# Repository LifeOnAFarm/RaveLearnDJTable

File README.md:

# Fisher-Price: Rave & Repeat DJ Table

A Raspberry Pi rebuild of a Fisher-Price kids' DJ table toy: an eight-key musical play
table running on a **Raspberry Pi Zero 2 W**, written in Python 3.11+.

Full run down of the hardware setup can be found [here](https://nastypieceof.work/raveandrepeat).
The PCB files, parts list and wiring notes are in [hardware/](hardware/README.md).

## Software guides

1. [Installation](docs/INSTALL.md): from a blank SD card to a finished table.
2. [Replacing sounds](docs/SAMPLES.md): songs, words, beats, drums, the recording prompt
   and announcements.

## What it does

The table has three keyboard modes, chosen on its web page or by holding the mode button
for 5 seconds.

**Learning.** The keys say their colour and shape in English (Level 1) or Irish (Level 2),
or play notes (Level 3). The **NumPad** (the single button made to look like a number pad)
plays a random song. Record asks for a message, records
3 seconds of your voice and plays it back as a pitched-up remix over a beat. There are four
music themes, each with its own instruments, songs and beats: **Teenage Disco, House, Punk
and Baby Raver**. A tap on the mode button changes theme.

**Music Maker.** Build a loop in three layers: melody (Level 1), drums (Level 2) and your
own voice as an instrument (Level 3).

**Bluetooth.** Phone music plays through the table and the keys play along.

| Control | Learning | Music Maker | Bluetooth |
| --- | --- | --- | --- |
| Keys | Colour/shape words or notes | Notes, drums or your voice | Notes over the music |
| Level | 1 English, 2 Irish, 3 notes | 1 melody, 2 drums, 3 voice | 1 Punk, 2 Teenage Disco, 3 House sounds |
| Tone | Three sounds per theme | Three instruments, kits or voice characters | Three instruments |
| Volume | Low / medium / high | Low / medium / high | Low / medium / high |
| Record | Voice remix | Hold: record a layer after the count-in. Tap at Level 3: sample a sound to play on the keys | Off |
| NumPad | Random song, or stop | Tap: play/pause. Hold 2 s: clear this layer. Hold 5 s: clear all | Tap: play/pause. Hold: next track |
| Platter | Bends notes and song speed; spun on its own, plays a scratch | Bends notes and loop speed | |

Spoken announcements say when the theme, mode or Level changes.

**Turning it off:** hold the mode button, then Record as well, and keep both held for
10 seconds. The table says it's shutting down and powers off safely. Wait for the Pi's
light to stop flashing before you switch off the power.

In Bluetooth mode the table is visible as **DJTable** for two minutes. Pair with no PIN.
If no phone connects in time, it goes back to Learning.

## Web pages

Open `http://<your-table>:8080` from a phone or computer on the same network.

- **Home:** keyboard mode, music theme and song uploads.
- **Admin:** live test of every button, slider, the platter and the microphone, plus each
  theme's song list.
- **Wi-Fi:** join a new network. If the table can't find a known network, it offers its
  own **DJTable-Setup** network (see the install guide).

## Sounds

Every sound the table needs is in `sounds/`, except the random songs, which you upload
yourself. There are **no commercial songs, licensed samples or personal recordings**.

- The keyboard instruments for every theme (House has chords, stabs and a deep bass in
  F minor) and the remix beats: original, synthesised in code.
- The English and Irish colour and shape words, the spoken announcements and the
  recording prompt.
- The platter scratches.

The Music Maker drum kits are built by the app itself when it starts.

Make the table your own with [Replacing sounds](docs/SAMPLES.md).

## Folder layout

```text
djtable/        the app: audio engine, buttons, platter, web pages
deploy/         install scripts, services, sound overlay
tools/          song volume matcher
sounds/         all of the table's sounds
docs/           install and sound guides
hardware/       PCB Gerbers, schematic, KiCad project, parts list and 3D prints
config.example.json   the table's settings (copied to config.json on install)
```

On the Pi, `config.json`, `assets/` (sounds) and `data/` (songs, recordings, loops) are
created by the installer and are never part of the repository.

## Licence

> Unofficial hobby project. Not affiliated with, endorsed by or sponsored by Fisher-Price
> or Mattel. Fisher-Price is a trademark of its owner, used here only to describe the toy
> this project rebuilds.

MIT source; see [LICENSE](LICENSE). Your own songs and sounds keep their own licences.

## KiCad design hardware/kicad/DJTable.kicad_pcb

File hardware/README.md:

# Hardware

The carrier PCB that turns the toy into a Rave & Repeat table. The full build, with
photos, is on the [project website](https://nastypieceof.work/raveandrepeat).

| File | What it is |
| --- | --- |
| `DJTable-gerbers.zip` | Ready to upload to a PCB maker (JLCPCB, PCBWay and others): copper, mask, silkscreen, outline and drill files. 2 layers. |
| `DJTable-schematic.pdf` | The schematic, for reading without KiCad. |
| `kicad/` | The KiCad 10 project (schematic, PCB and its own footprint library), if you want to change the board. Open `DJTable.kicad_pro`. |

## Read before you build

This is the board revision that was built and works, with these fixes made by hand.
**The PCB files don't include them yet.**

1. **Wire the amp's SD pin to Raspberry Pi header pin 7** (GPIO4). That's pin 7 of the
   Pi's 40-pin header, not of the amp module. The software uses it to mute the amp while
   it loads a new theme. Without it, theme changes crackle.
2. **Wire the amp's GAIN pin to ground.** This sets the amp to 12 dB, louder than the
   9 dB it gives with GAIN left unconnected.
3. **The Raspberry Pi mounts upside-down**, with its chips facing the carrier board. Oops
4. **The toy's original switches don't fit this board**, although that was the plan.
   Use these instead. Both fit the board and work with the toy:
   - **SS-23D03-G4** three-position slide switches for Level and Volume (SW4, SW5).
     They stand about 2 mm taller than the toy's switches, so print the new
     `Switch Cover.STL` (below), or cut about 2 mm off the toy's own switch covers;
   - **PS-12F03-G5** push switches for the three Tone buttons (SW1–SW3). The G4 also
     works, but its shorter plunger needs the board lined up exactly before screwing it in.
5. **Bridge R2** with a 0 Ω resistor or a wire. It connects the Mode button; it was left
   as an option on this board and isn't needed as a resistor.

**For a future board revision:** pick a different three-position slide switch for Level and
Volume, with a body about 5.5 mm tall instead of the SS-23D03-G4's 7.5 mm, so the toy's
original switch covers fit unchanged. No replacement part has been chosen yet.

## Parts

| Qty | Ref | Part | Notes |
| ---: | --- | --- | --- |
| 1 | U1 | Raspberry Pi Zero 2 W | With a 2×20 male header |
| 1 | U1 | 2×20 female socket, 2.54 mm | |
| 1 | U2 | INMP441 microphone module | |
| 1 | U3 | MAX98357A amplifier module (Adafruit-style) | Plus the SD and GAIN wires above |
| 3 | SW1–SW3 | PS-12F03-G5 push switch | Tone |
| 2 | SW4–SW5 | SS-23D03-G4 slide switch, 3-position | Level and Volume; needs the printed switch covers |
| 2 | SW6–SW7 | 6×6 mm tactile switch, through-hole | Record and Mode |
| 1 | R1 | 330 Ω, 1206 | NumPad LED |
| 1 | R2 | 0 Ω, 1206, or a wire | **Bridge it**: connects the Mode button |
| 2 | R6–R7 | 33 Ω, 1206 | I2S clock lines |
| 3 | C2, C3, C4 | 100 nF ceramic, 1206, 16 V+ | |
| 1 | C1 | 220 µF 10 V electrolytic | |
| 1 | C5 | 47 µF 10 V electrolytic | |
| 1 | F1 | Resettable fuse, 2 A hold, 6 V+, 1812 | |
| — | J1–J6 | 2.54 mm pin headers, or solder the wires in | See connectors below |

Off the board:
- an AS5600 magnetic angle module with a diametric magnet, for the platter;
- USB C connector.
- 3D printed parts (below).

Power the table only through J3, never through the Pi's USB port at the same time.

## 3D printed parts

STL files in [`3d-prints/`](3d-prints/).

| Part | What it does | Needed? |
| --- | --- | --- |
| `Platter Mount.STL` | Replaces the toy's platter mount, with a pocket to glue in the AS5600's magnet | Yes |
| `AS5600 Mount.STL` | Holds the AS5600 under the platter; takes a 5 mm LED too if you want one. Replaces the toy's button and LED board | Yes |
| `Mode Button.STL` | A working Mode button. On Learn & Play tables without language changing, that button is only a dummy | Only for those tables |
| `Switch Cover.STL` | Covers for the Level and Volume switches, made for the taller SS-23D03-G4 | Yes, unless you cut about 2 mm off the toy's own covers |
| `Speaker Holder.STL` | Lets you fit a more powerful speaker in place of the original | Optional |

## Connectors

| Connector | Pins |
| --- | --- |
| J1 Keyboard | 1 GND, 2 pink, 3 red, 4 orange, 5 green, 6 yellow, 7 blue, 8 purple, 9 black |
| J2 NumPad button | 1 switch GND, 2 switch, 3 LED −, 4 LED + |
| J3 Power in | 1 +5 V, 2 GND |
| J4, J5 | Spare 5 V outputs (1 +5 V, 2 GND) |
| J6 AS5600 | 1 VCC (3.3 V), 2 OUT (unused), 3 GND, 4 DIR (GND), 5 SCL, 6 SDA, 7 GPO (unused) |

## Raspberry Pi pins

All buttons and switches connect a pin to ground; the software turns on the pull-ups.

| Control | GPIO (BCM) | Header pin |
| --- | --- | --- |
| Keys pink, red, orange, green | 5, 6, 12, 13 | 29, 31, 32, 33 |
| Keys yellow, blue, purple, black | 16, 17, 22, 27 | 36, 11, 15, 13 |
| Tone 1 / 2 / 3 | 7 / 24 / 23 | 26 / 18 / 16 |
| Level 1 / 2 / 3 | 8 / 26 / 25 | 24 / 37 / 22 |
| Volume low / medium / high | 15 / 14 / 9 | 10 / 8 / 21 |
| NumPad | 10 | 19 |
| Record | 11 | 23 |
| Mode | 0 | 27 |
| Amp mute (amp SD) | 4 | 7 |
| I2S bit clock / frame clock | 18 / 19 | 12 / 35 |
| Mic data / speaker data | 20 / 21 | 38 / 40 |
| AS5600 SDA / SCL | 2 / 3 | 3 / 5 |

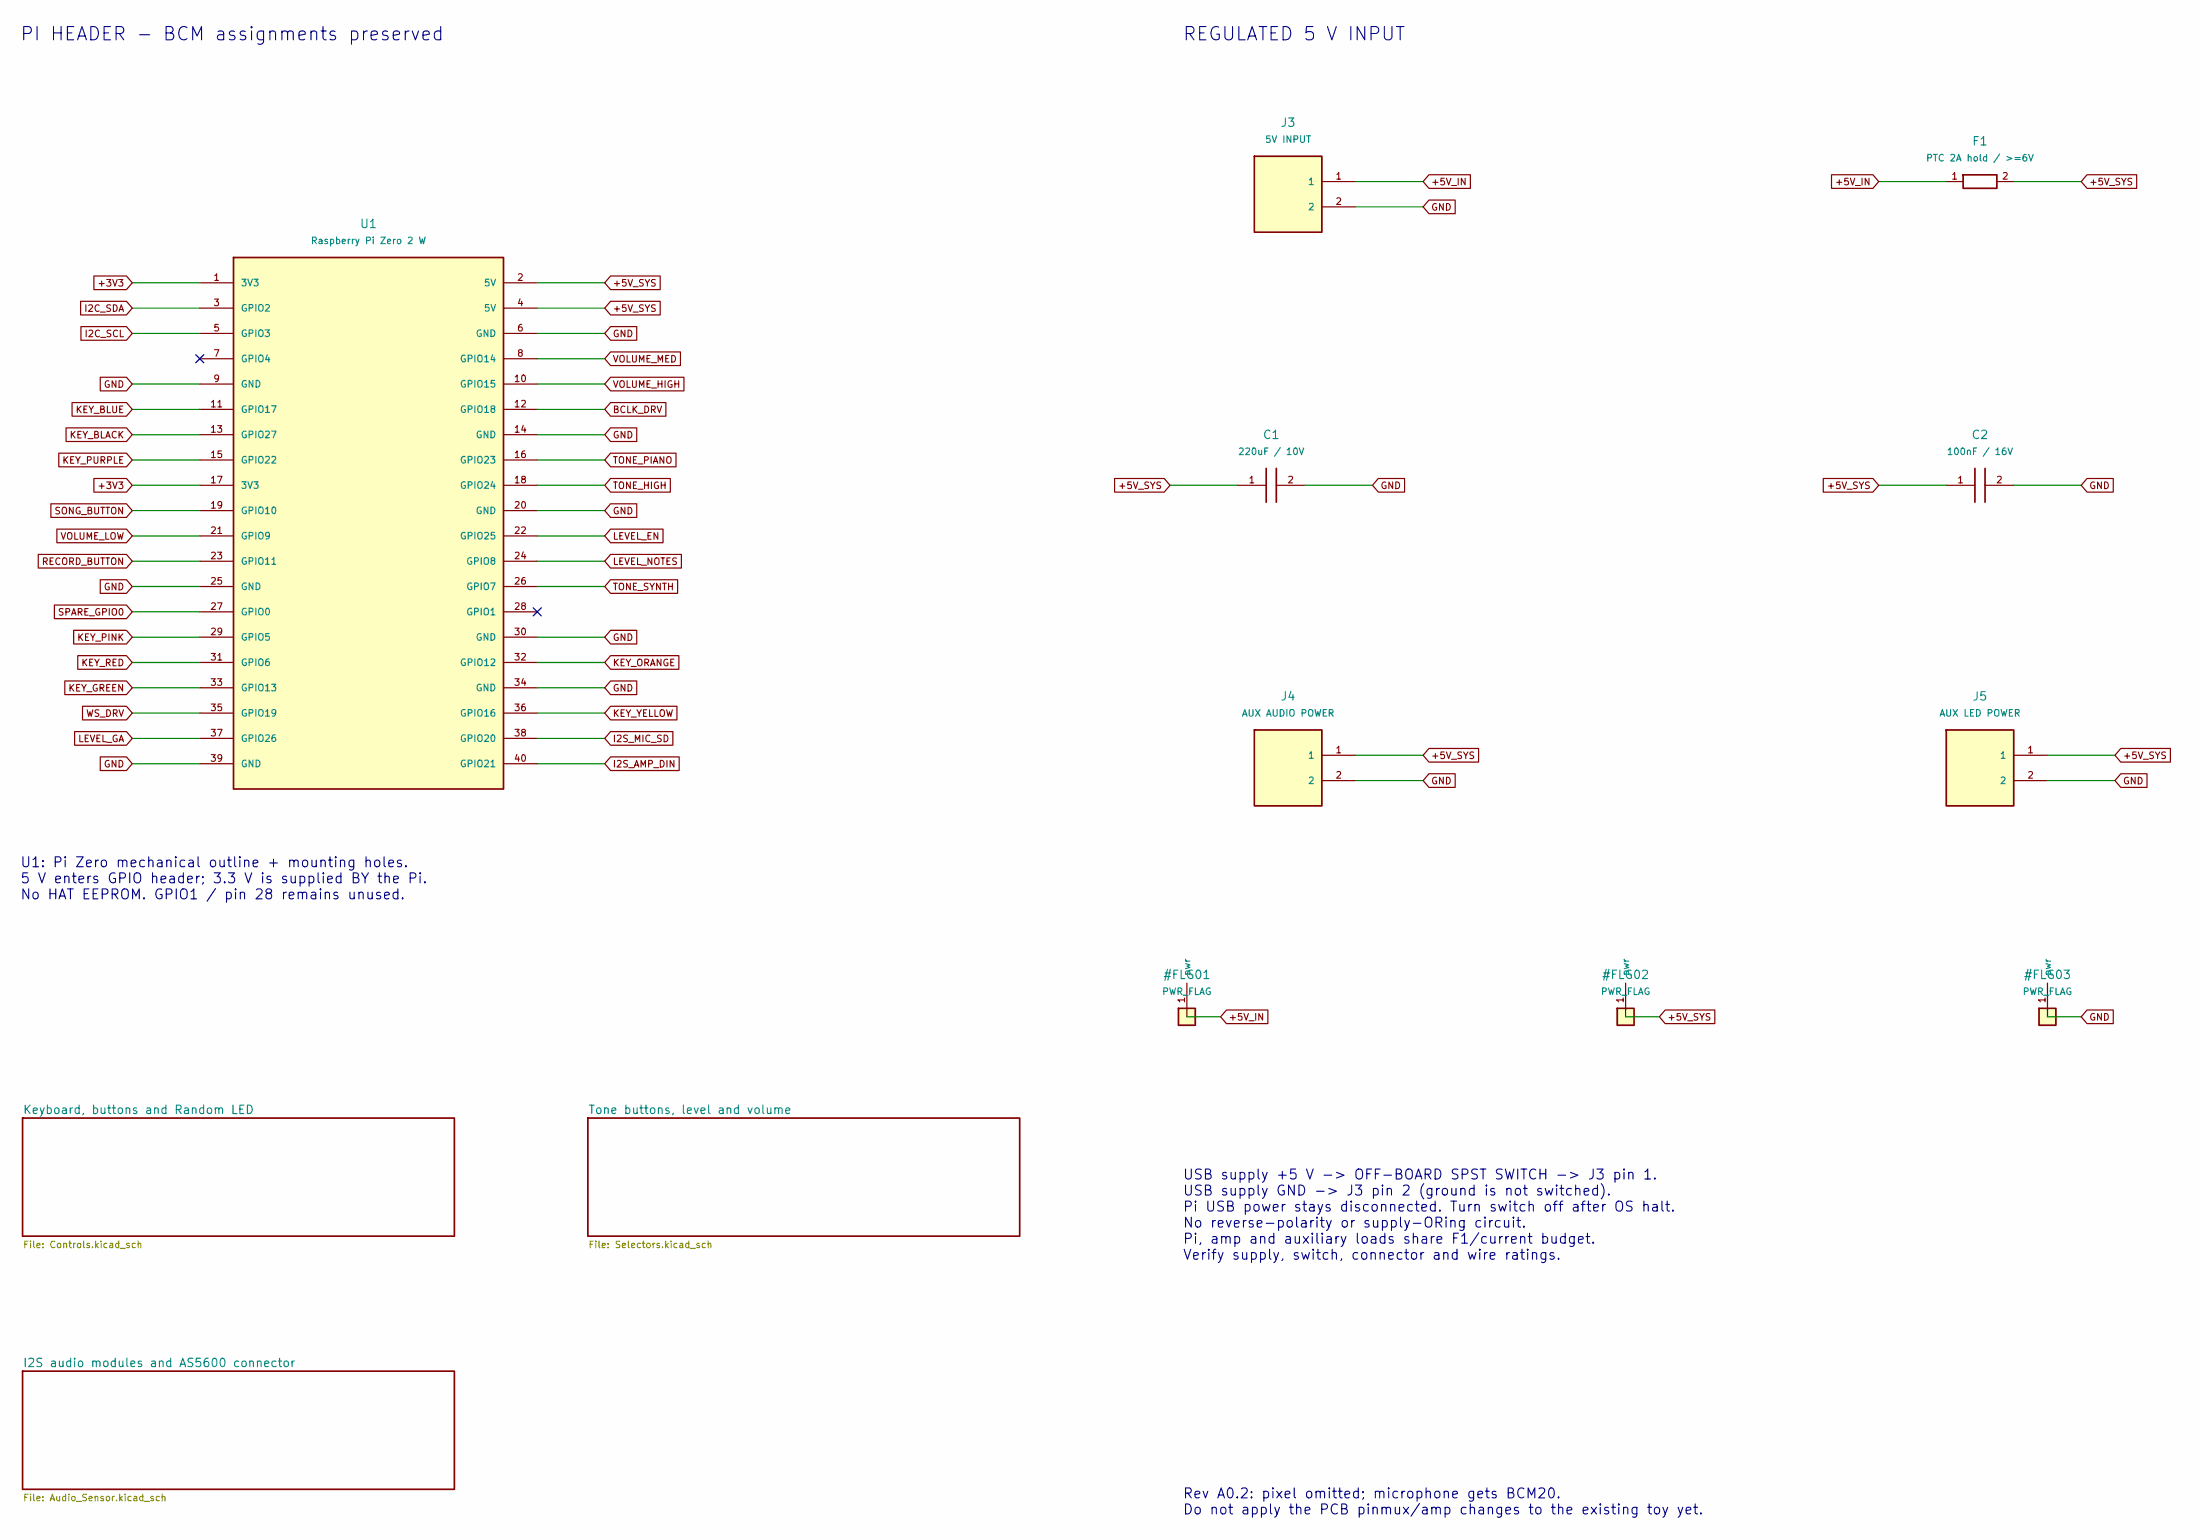
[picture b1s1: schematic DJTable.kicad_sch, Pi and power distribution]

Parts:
C1: 220uF / 10V; CP_Radial_D8.0mm_P3.50mm
C2: 100nF / 16V; C_1206_3216Metric_Pad1.33x1.80mm_HandSolder
F1: PTC 2A hold / >=6V; Fuse_1812_4532Metric
J3: 5V INPUT; PinHeader_1x02_P2.54mm_Vertical
J4: AUX AUDIO POWER; PinHeader_1x02_P2.54mm_Vertical
J5: AUX LED POWER; PinHeader_1x02_P2.54mm_Vertical
U1: Raspberry Pi Zero 2 W; Raspberry_Pi_Zero_Socketed_THT_FaceDown_MountingHoles

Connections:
+3V3: U1.1 (3V3), U1.17 (3V3); also elsewhere on the board
+5V_IN: F1.1, J3.1
+5V_SYS: C1.1, C2.1, F1.2, J4.1, J5.1, U1.2 (5V), U1.4 (5V); also elsewhere on the board
BCLK_DRV: U1.12 (GPIO18); also elsewhere on the board
GND: C1.2, C2.2, J3.2, J4.2, J5.2, U1.6 (GND), U1.9 (GND), U1.14 (GND), U1.20 (GND), U1.25 (GND), U1.30 (GND), U1.34 (GND), U1.39 (GND); also elsewhere on the board
I2C_SCL: U1.5 (GPIO3); also elsewhere on the board
I2C_SDA: U1.3 (GPIO2); also elsewhere on the board
I2S_AMP_DIN: U1.40 (GPIO21); also elsewhere on the board
I2S_MIC_SD: U1.38 (GPIO20); also elsewhere on the board
KEY_BLACK: U1.13 (GPIO27); also elsewhere on the board
KEY_BLUE: U1.11 (GPIO17); also elsewhere on the board
KEY_GREEN: U1.33 (GPIO13); also elsewhere on the board
KEY_ORANGE: U1.32 (GPIO12); also elsewhere on the board
KEY_PINK: U1.29 (GPIO5); also elsewhere on the board
KEY_PURPLE: U1.15 (GPIO22); also elsewhere on the board
KEY_RED: U1.31 (GPIO6); also elsewhere on the board
KEY_YELLOW: U1.36 (GPIO16); also elsewhere on the board
LEVEL_EN: U1.22 (GPIO25); also elsewhere on the board
LEVEL_GA: U1.37 (GPIO26); also elsewhere on the board
LEVEL_NOTES: U1.24 (GPIO8); also elsewhere on the board
RECORD_BUTTON: U1.23 (GPIO11); also elsewhere on the board
SONG_BUTTON: U1.19 (GPIO10); also elsewhere on the board
SPARE_GPIO0: U1.27 (GPIO0); also elsewhere on the board
TONE_HIGH: U1.18 (GPIO24); also elsewhere on the board
TONE_PIANO: U1.16 (GPIO23); also elsewhere on the board
TONE_SYNTH: U1.26 (GPIO7); also elsewhere on the board
VOLUME_HIGH: U1.10 (GPIO15); also elsewhere on the board
VOLUME_LOW: U1.21 (GPIO9); also elsewhere on the board
VOLUME_MED: U1.8 (GPIO14); also elsewhere on the board
WS_DRV: U1.35 (GPIO19); also elsewhere on the board

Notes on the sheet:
PI HEADER - BCM assignments preserved
REGULATED 5 V INPUT
Rev A0.2: pixel omitted; microphone gets BCM20. Do not apply the PCB pinmux/amp changes to the existing toy yet.
USB supply +5 V -> OFF-BOARD SPST SWITCH -> J3 pin 1. USB supply GND -> J3 pin 2 (ground is not switched). Pi USB power stays disconnected. Turn switch off after OS halt. No reverse-polarity or supply-ORing circuit. Pi, amp and auxiliary loads share F1/current budget. Verify supply, switch, connect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
U1: Pi Zero mechanical outline + mounting holes. 5 V enters GPIO header; 3.3 V is supplied BY the Pi. No HAT EEPROM. GPIO1 / pin 28 remains unused.

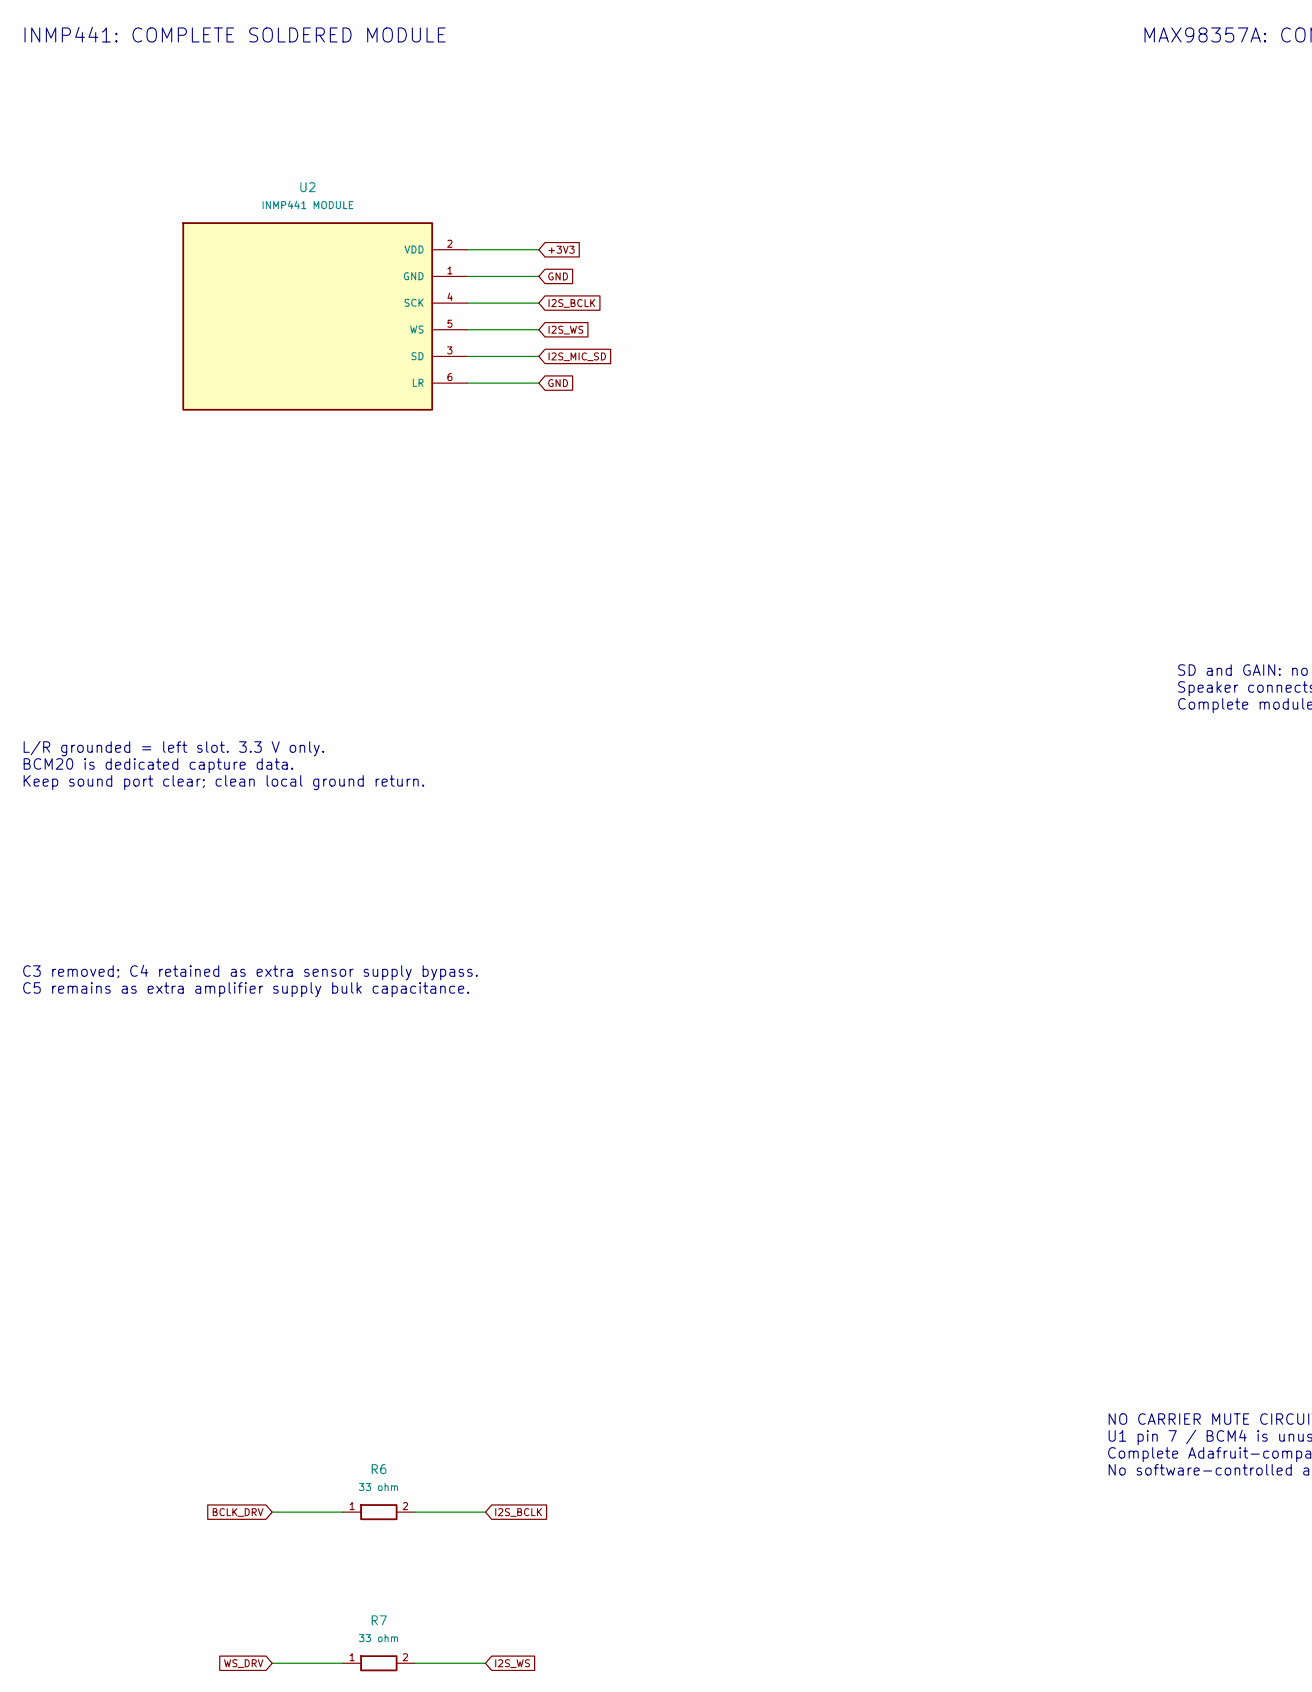
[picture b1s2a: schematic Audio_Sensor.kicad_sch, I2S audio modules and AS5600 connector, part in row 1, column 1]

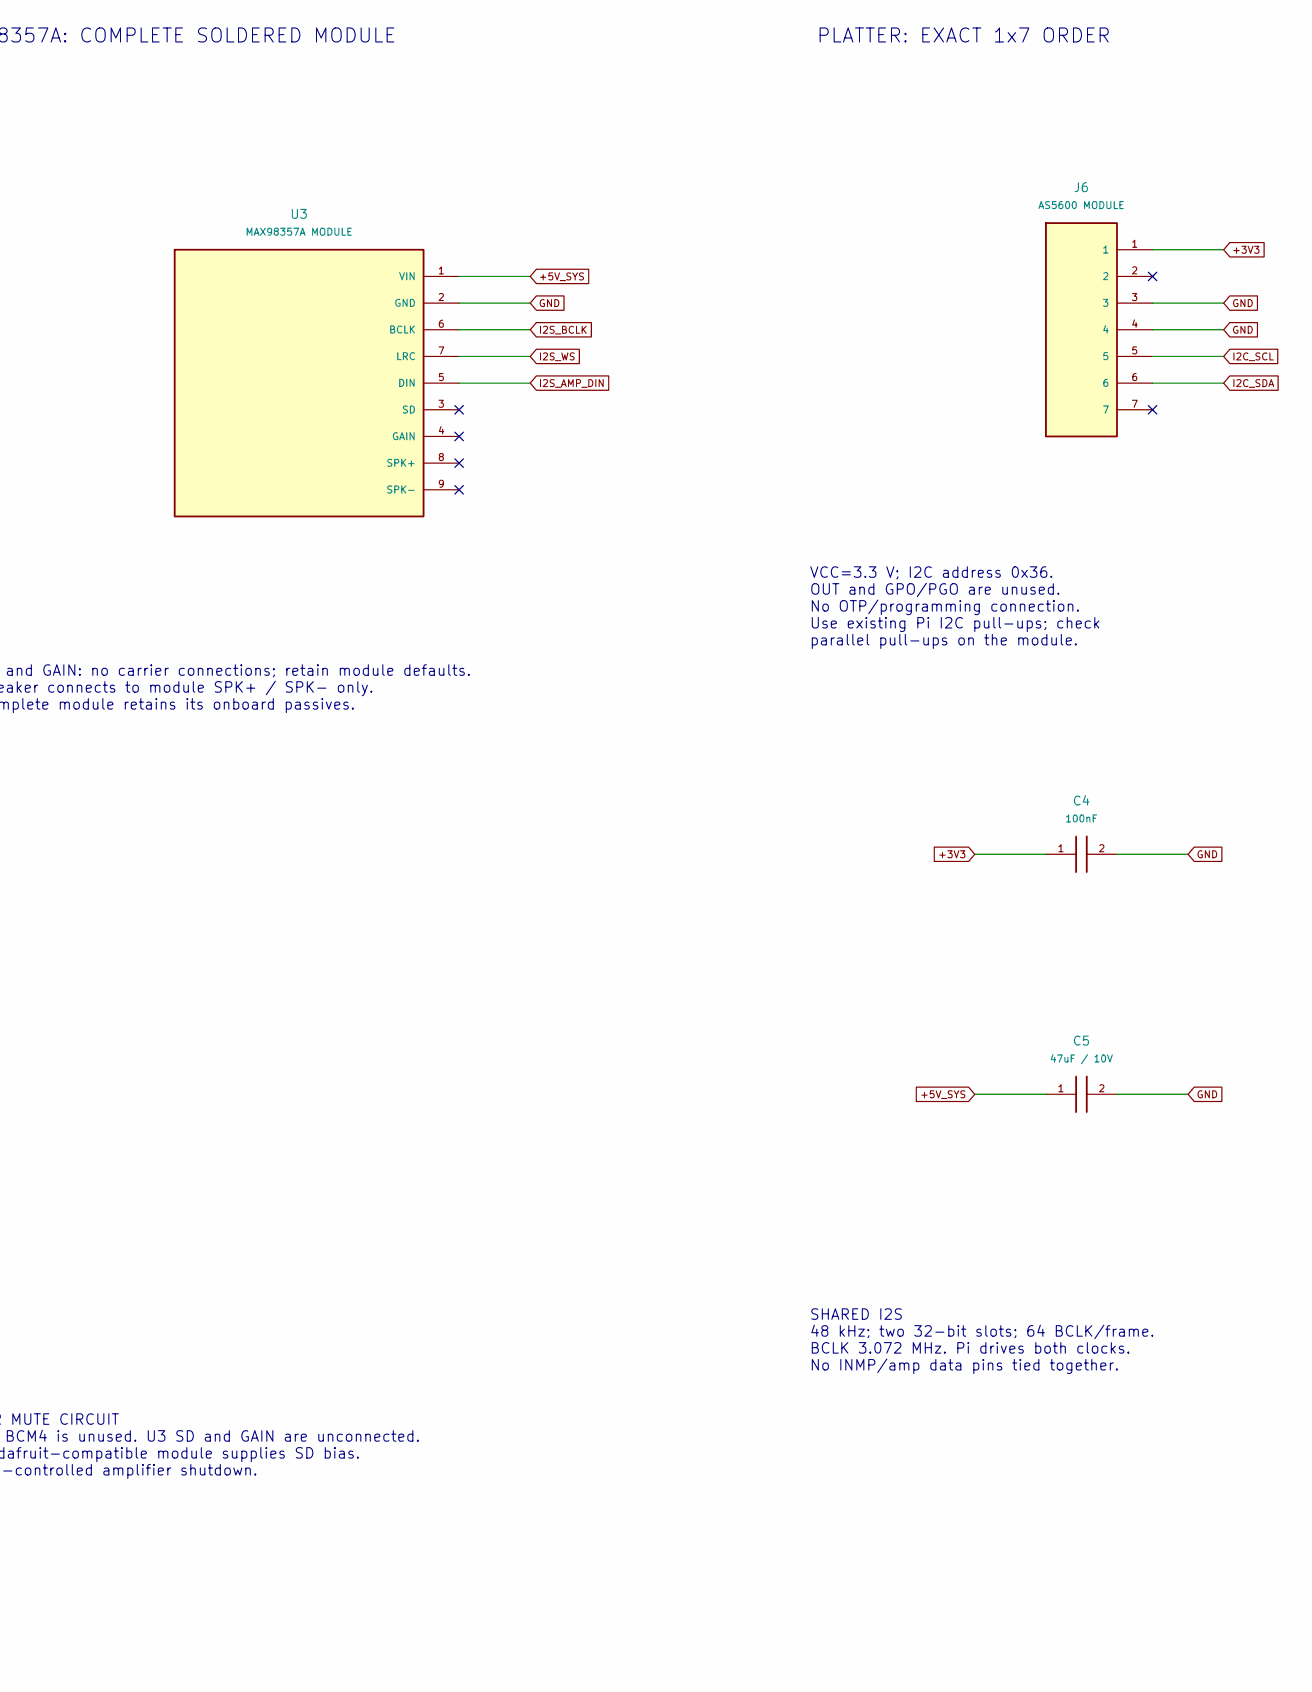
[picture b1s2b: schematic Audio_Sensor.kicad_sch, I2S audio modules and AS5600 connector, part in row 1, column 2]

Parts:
C4: 100nF; C_1206_3216Metric_Pad1.33x1.80mm_HandSolder
C5: 47uF / 10V; CP_Radial_D5.0mm_P2.00mm
J6: AS5600 MODULE; PinHeader_1x07_P2.54mm_Vertical
R6, R7: 33 ohm; R_1206_3216Metric_Pad1.30x1.75mm_HandSolder
U2: INMP441 MODULE; INMP441_Round_Module_2x3_P2.54_Row7.62
U3: MAX98357A MODULE; MAX98357_Adafruit_Module

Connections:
+3V3: C4.1, J6.1, U2.2 (VDD); also elsewhere on the board
+5V_SYS: C5.1, U3.1 (VIN); also elsewhere on the board
BCLK_DRV: R6.1; also elsewhere on the board
GND: C4.2, C5.2, J6.3, J6.4, U2.1 (GND), U2.6 (LR), U3.2 (GND); also elsewhere on the board
I2C_SCL: J6.5; also elsewhere on the board
I2C_SDA: J6.6; also elsewhere on the board
I2S_AMP_DIN: U3.5 (DIN); also elsewhere on the board
I2S_BCLK: R6.2, U2.4 (SCK), U3.6 (BCLK)
I2S_MIC_SD: U2.3 (SD); also elsewhere on the board
I2S_WS: R7.2, U2.5 (WS), U3.7 (LRC)
WS_DRV: R7.1; also elsewhere on the board

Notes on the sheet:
PLATTER: EXACT 1x7 ORDER
SD and GAIN: no carrier connections; retain module defaults. Speaker connects to module SPK+ / SPK- only. Complete module retains its onboard passives.
SHARED I2S 48 kHz; two 32-bit slots; 64 BCLK/frame. BCLK 3.072 MHz. Pi drives both clocks. No INMP/amp data pins tied together.
NO CARRIER MUTE CIRCUIT U1 pin 7 / BCM4 is unused. U3 SD and GAIN are unconnected. Complete Adafruit-compatible module supplies SD bias. No software-controlled amplifier shutdown.
INMP441: COMPLETE SOLDERED MODULE
VCC=3.3 V; I2C address 0x36. OUT and GPO/PGO are unused. No OTP/programming connection. Use existing Pi I2C pull-ups; check parallel pull-ups on the module.
MAX98357A: COMPLETE SOLDERED MODULE
L/R grounded = left slot. 3.3 V only. BCM20 is dedicated capture data. Keep sound port clear; clean local ground return.
C3 removed; C4 retained as extra sensor supply bypass. C5 remains as extra amplifier supply bulk capacitance.

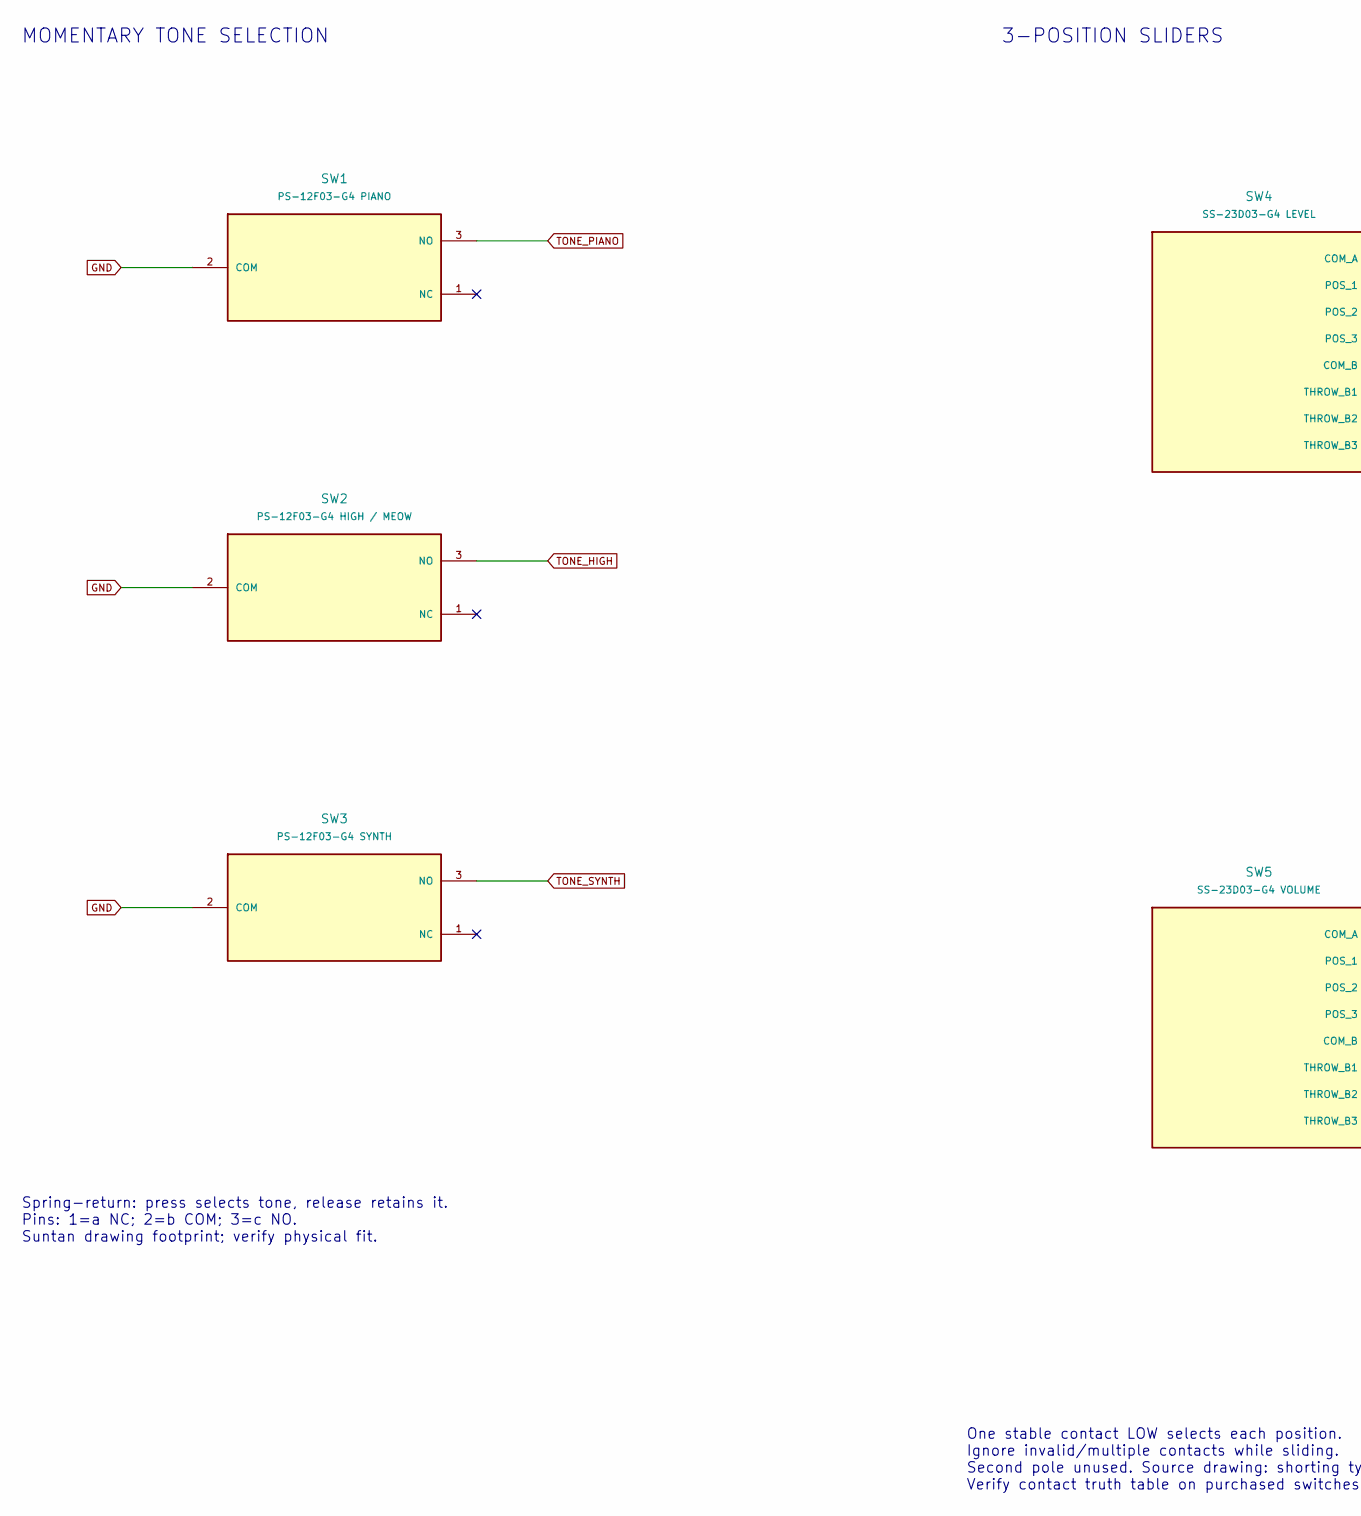
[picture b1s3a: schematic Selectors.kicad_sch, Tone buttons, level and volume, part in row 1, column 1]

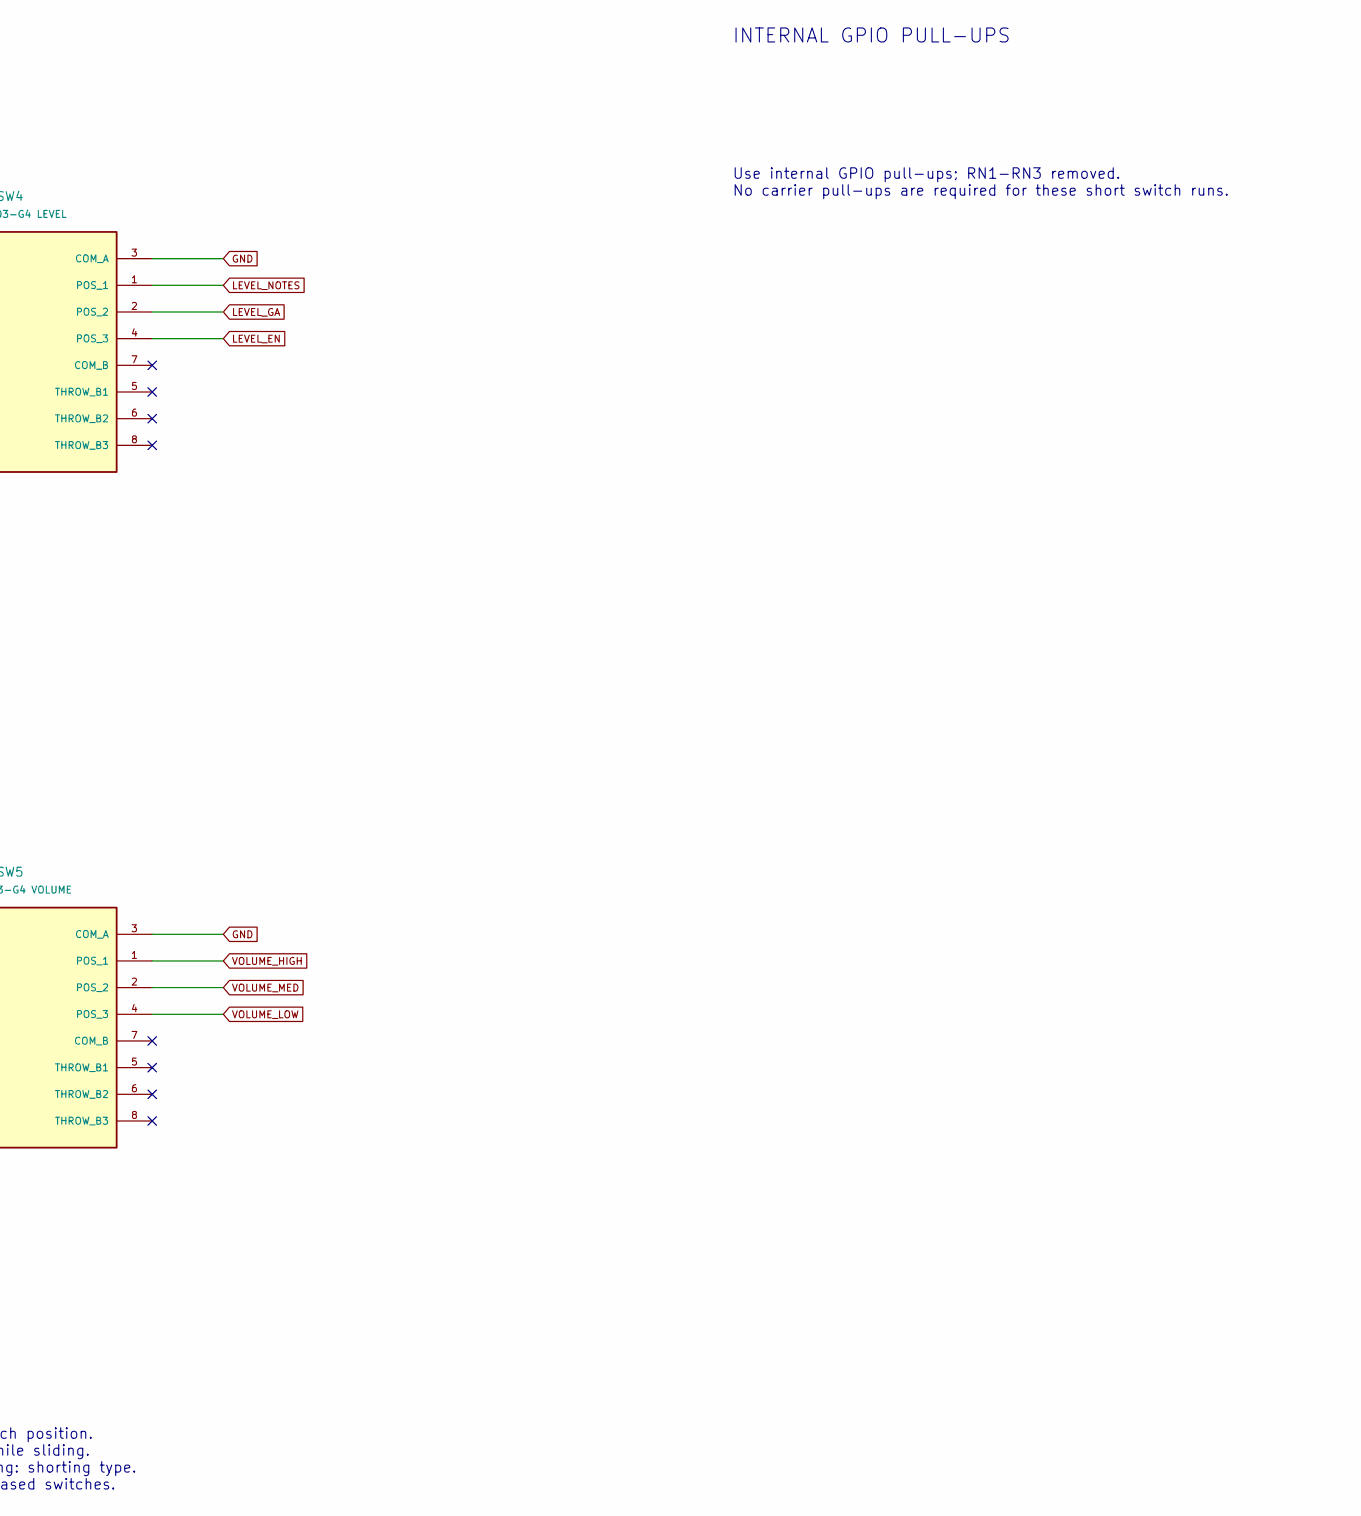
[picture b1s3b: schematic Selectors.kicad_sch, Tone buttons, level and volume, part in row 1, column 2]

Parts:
SW1: PS-12F03-G4 PIANO; PS12F03_Momentary_3Pin_P3.2
SW2: PS-12F03-G4 HIGH / MEOW; PS12F03_Momentary_3Pin_P3.2
SW3: PS-12F03-G4 SYNTH; PS12F03_Momentary_3Pin_P3.2
SW4: SS-23D03-G4 LEVEL; SS23D03_G4_2P3T_P2_P4
SW5: SS-23D03-G4 VOLUME; SS23D03_G4_2P3T_P2_P4

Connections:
GND: SW1.2 (COM), SW2.2 (COM), SW3.2 (COM), SW4.3 (COM_A), SW5.3 (COM_A); also elsewhere on the board
LEVEL_EN: SW4.4 (POS_3); also elsewhere on the board
LEVEL_GA: SW4.2 (POS_2); also elsewhere on the board
LEVEL_NOTES: SW4.1 (POS_1); also elsewhere on the board
TONE_HIGH: SW2.3 (NO); also elsewhere on the board
TONE_PIANO: SW1.3 (NO); also elsewhere on the board
TONE_SYNTH: SW3.3 (NO); also elsewhere on the board
VOLUME_HIGH: SW5.1 (POS_1); also elsewhere on the board
VOLUME_LOW: SW5.4 (POS_3); also elsewhere on the board
VOLUME_MED: SW5.2 (POS_2); also elsewhere on the board

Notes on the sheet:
Spring-return: press selects tone, release retains it. Pins: 1=a NC; 2=b COM; 3=c NO. Suntan drawing footprint; verify physical fit.
MOMENTARY TONE SELECTION
3-POSITION SLIDERS
INTERNAL GPIO PULL-UPS
One stable contact LOW selects each position. Ignore invalid/multiple contacts while sliding. Second pole unused. Source drawing: shorting type. Verify contact truth table on purchased switches.
Use internal GPIO pull-ups; RN1-RN3 removed. No carrier pull-ups are required for these short switch runs.
